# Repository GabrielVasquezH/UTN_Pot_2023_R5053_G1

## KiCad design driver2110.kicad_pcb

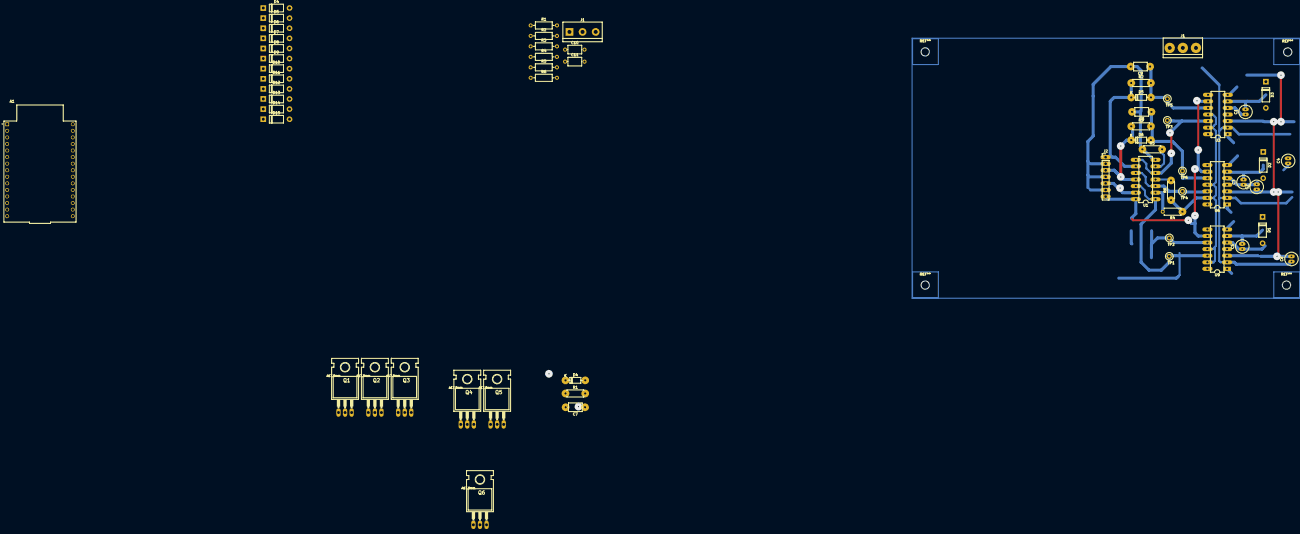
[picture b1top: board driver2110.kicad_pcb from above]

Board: 2 copper layers, 61 parts (0 on the bottom side), 47 nets.

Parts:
A1: ESP32_DevKit_V1_DOIT_30GPIOs; MODULE_ESP32-DEVKITC
C1, C2, C3, C4, C5, C6: 10UF; C_Radial_D5.0mm_H7.0mm_P2.00mm
C7, C8, C9: 560pf; C_Axial_L5.1mm_D3.1mm_P7.50mm_Horizontal
C10: 10uf; C_Axial_L5.1mm_D3.1mm_P7.50mm_Horizontal
C11: 0.1uf; C_Axial_L5.1mm_D3.1mm_P7.50mm_Horizontal
D1, D2, D3: 1N4001; P1_DO-41
D4, D5#2, D6: 1N4148; D_DO-35_SOD27_P7.62mm_Horizontal
D4#2, D6#2, D8, D10, D12, D14: 1N4148; P1_DO-41
D5, D7, D9, D11, D13, D15: 1N4007; P1_DO-41
J1, J1#2: Screw_Terminal_01x03; TerminalBlock_bornier-3_P5.08mm
J2: Conn_01x07_Male; PinHeader_1x07_P2.54mm_Vertical
Q1, Q2, Q3, Q4, Q5, Q6: IRF840; TO220
R1, R2#2, R3, R4#2, R5, R6: Resistor; R_Axial_DIN0207_L6.3mm_D2.5mm_P10.16mm_Horizontal
R1#2, R2, R3#2: 100; R_Axial_DIN0207_L6.3mm_D2.5mm_P7.62mm_Horizontal
R4, R5#2, R6#2: 10k; R_Axial_DIN0207_L6.3mm_D2.5mm_P7.62mm_Horizontal
TP1, TP2, TP3, TP4, TP5, TP6: TestPoint; TestPoint_Loop_D1.80mm_Drill1.0mm_Beaded
U1: 74HC14; DIP-14_W7.62mm
U3, U6, U9: IR2110; DIP-14_W7.62mm

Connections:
/INHA: A1.14 (D22/SCL), TP5.1, U3.10 (HIN)
/INHB: A1.23 (DAC1/ADC2_CH8/D25), TP6.1, U6.10 (HIN)
/INHC: TP2.1, U9.10 (HIN)
/INLA: A1.19 (ADC1_CH6/D34), TP3.1, U3.12 (LIN)
/INLB: A1.21 (ADC1_CH4/D32), TP4.1, U6.12 (LIN)
/INLC: TP1.1, U9.12 (LIN)
GND: C2.1, C4.1, C6.1, D7.2 (A), D11.2 (A), D13.2 (A), J1.1, Q2.3 (S), Q4.3 (S), Q5.3 (S), U3.2 (COM), U6.2 (COM), U9.2 (COM)
unnamed: D4.2 (A), R1#2.2
unnamed: D6.2 (A), R3#2.2
unnamed: D5#2.2 (A), R2.2
unnamed: C6.2, D1.2 (A), U9.3 (VCC)
unnamed: C5.2, D1.1 (K), U9.6 (VB)
unnamed: C4.2, D2.2 (A), U6.3 (VCC)
unnamed: C3.2, D2.1 (K), U6.6 (VB)
unnamed: C2.2, D3.2 (A), U3.3 (VCC)
unnamed: C1.2, D3.1 (K), U3.6 (VB)
unnamed: D4#2.2 (A), Q1.1 (G), R1.2
unnamed: D4#2.1 (K), R1.1, U3.7 (HO)
unnamed: D4.1 (K), J2.5, R1#2.1, U1.13
unnamed: D5.2 (A), D7.1 (K), J1#2.1
unnamed: D5#2.1 (K), J2.1, R2.1, U1.9
unnamed: D6#2.2 (A), Q2.1 (G), R2#2.2
unnamed: D6#2.1 (K), R2#2.1, U3.1 (LO)
unnamed: D6.1 (K), J2.3, R3#2.1, U1.11
unnamed: D8.2 (A), Q3.1 (G), R3.2
unnamed: D8.1 (K), R3.1, U6.7 (HO)
unnamed: D10.2 (A), Q4.1 (G), R4#2.2
unnamed: D10.1 (K), R4#2.1, U6.1 (LO)
unnamed: D9.2 (A), D11.1 (K), J1#2.2
unnamed: D12.2 (A), Q5.1 (G), R5.2
unnamed: D12.1 (K), R5.1, U9.1 (LO)
unnamed: D13.1 (K), D15.2 (A)
unnamed: D14.2 (A), Q6.1 (G), R6.2
unnamed: D14.1 (K), R6.1, U9.7 (HO)
unnamed: C5.1, J1#2.3, U9.5 (VS)
unnamed: Q1.3 (S), Q2.2 (D)
unnamed: C3.1, Q3.3 (S), Q4.2 (D), U6.5 (VS)
unnamed: Q5.2 (D), Q6.3 (S)
unnamed: R4.2, U1.2
unnamed: R5#2.2, U1.6
unnamed: R6#2.2, U1.4
unnamed: U1.1, U1.12
unnamed: U1.5, U1.8
unnamed: U1.3, U1.10
unnamed: C1.1, U3.5 (VS)
VCC: C7.1, C8.1, C9.1, C10.1, C11.1, D5.1 (K), D9.1 (K), D15.1 (K), J2.7, Q1.2 (D), Q3.2 (D), Q6.2 (D), U1.14 (VCC), U3.9 (VDD), U6.9 (VDD), U9.9 (VDD)
VSS: A1.2 (GND), A1.29 (GND), C7.2, C8.2, C9.2, C10.2, C11.2, J2.2, J2.4, J2.6, R4.1, R5#2.1, R6#2.1, U1.7 (GND), U3.11 (SD), U3.13 (VSS), U6.11 (SD), U6.13 (VSS), U9.11 (SD), U9.13 (VSS)

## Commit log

2023-10-28 primer commit
2023-11-01 Correccion en la comprobacion del esquematico
    para corregir los errores, se agregaron librerías, modificaron los cableados y se pusieron test points
